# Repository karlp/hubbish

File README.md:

## Hubbish is not rubbish.

Hubbish is a USB 2.0 HS hub.  And?  It has per port power switching and overrcurrent shutoff.
And? It is designed for cascading, with 6 ports for user devices on the front, and ports
on each side for directly plugging together.  And? That's it.

## but why.gif?

Per port power switching was a goal.  Also, "this should be really simple!"
Also, to make the physical layout sensible for the desired use case.  Initially, this
project was conceived to be part of regression testing the USB stack for
[libopencm3](http://www.libopencm3.org).  The _minimal_ test setup there required 17
USB devices.  This is also why the ports are paired.  It's setup to have one port
for the DUT and one for the test driver.  They are otherwise completely independent.

That's all folks!

## Design goals
Cheap as shit, but fully functional. So, cheapest china compatible parts for everything,
but to avoid running into hub depth limits, and make config simpler, still using a
7 port hub, not attempting to cascade 4 port hubs.  Given that the original design goal requires
3 stacked hubs for 18 test ports, caascading hubs internally was not appealing.

Still, doing usb-hs on 2 layers requires fat traces and isolation to do properly, so this
setup is currently targetting jlcpcb's cheap as shit 4 layer 2313 stackup.

Oh, and design it to actually go in a case.

## Origins
This project was split out from the [libopencm3-tests](http://github.com/karlp/libopencm3-tests)
repository when it became apparent that it was it's own monster.

## Versions
### "r4" r2022-12
#### Status
Only on paper, mostly, uses a proper matched pair to "correctly" implement the auto vbus/5v switchiver. (I misunderstood the use of the matched pair, and just used two discrete transistors in overzealous BOM optimization.
TBD: fixes the pwoer good indicator on the main supply as well?
Still need to work on the "local power" portion a bit more fully? (or double check it?)

### "r3" r2022-10
#### Improvements
After a long hiatus, I decided to get back to it, and not even bother assembling the r2 boards I had gotten back.  I had already found some errors, which I can't remember entirely right now, so we just moved forward to r3:
This has a very overhauled BOM, to match JLC's assembly service, rather than just something to assemble myself by hand.
Some footprints change to suit this as well.

#### Status
This was built and assembled by JLC.  It works ok. It doesn't switch between bus powered and self powered very well, iirc.  The hub's "local power" flag isn't handled properly, and that's just my error.  The board still uses optional A-male or B-micro for the upstream USB connection, and "obviously" that should all be PD and type-C these days :)  maybe one day...
Finally, the dual colour leds chosen aren't really very good at showing two colours for low speed / full speed / high speed, particular the difference between FS and HS, which is the more interesting one.  Should revisit that, but I had enough on with this revision to not do more. The "Power Good" LED for the onboard DCDC supply doesn't work properly either, again, my error,  but not really critical.  Finally, the polarity protection FET is only rated to Vgs of 30V.  It's suggested (rightly) that this is really pushing it for a 24V design, and I should look for a better option there.

But, the 40W supply works! This is the biggest DCDC supply I'd ever made myself. (FIXME - add the picture of all the usb load testers plugged in) And not just works, it works and keeps cool, and you can deliver all that power to all 7 downstream ports, up to the limit of each of the load switches.

This design also just decided that programming the EEPROM was the _right_ thing to do, as it also lets you arrange the LEDs nicely to match the ports, and provide proper serial numbers, which are also an important part of a big cascaded port power switching design. [generatei2c.py] is a python script that generates commands for use with i2cutils to program the eeprom via the header.  I used the [i2c_tools example](https://github.com/espressif/esp-idf/tree/master/examples/peripherals/i2c/i2c_tools) on an ESP32 devboard to do this.  It's... very simplistic, but it's enough.

* 
* [Schematic-r3](r2022-10/hubbish-rev3-2022-10.pdf)
* Load testing all ports at once.  (I have thermal images, but have lost them... will have to retest)

### "r2" r2021-03  (lol, finished and ordered 2022-06)
#### Improvements:
Adds a 30-40ish Watt power supply.  Inductor is rated to 9A, regulator to 12A. Per port power switches are
still 1A nominal, so nominally 7x5x1 = 35W for the ports plus around .5x3.3 for the hub itself, or an extra say 2W.

Resizes to 100x80mm so cheaper manufacturing again.  We're no longer trying to find an off the shelf case.
Places like 3d craft cloud have gotten so cheap I'm going to just make a custom case and have it printed on demand.

What's it look like?

* [Schematic-r2](r2021-02/hubbish-rev2.pdf)

#### Bugs
This doesn't have ground connected for two caps on the 3v3 rail, and would have needed some bodge wires, but I seem to recall there being something else, to the point that I decided to not even bother assembling it, and just move on to a rev3, designed for JLC assembly.

### r2020-03
What's it look like?

* [Schematic-r1](r2020-03/usb-test-harness.pdf)

#### Bugs

1. Missing a serial resistor for the crystal.  Doesn't enumerate the hub without it.
1. Needs a jumper wire if yout want to actually run it as a bus powered hub for testing.
1. Port numbers are super wonky.
1. .... doesn't actually work?  I suspect I just have assembly issues, but...
1. Bigger than 100x100, which fits the Bud case nicely, and didn't matter when 4L was always just size based
   but now that jlc is doing 4L super cheap for under 100x100, this can be considered a bug
1. vertical (z axis) positioning of the usptream usb-a-male and downstream usb-a-female for chaining doesn't
   align properly.

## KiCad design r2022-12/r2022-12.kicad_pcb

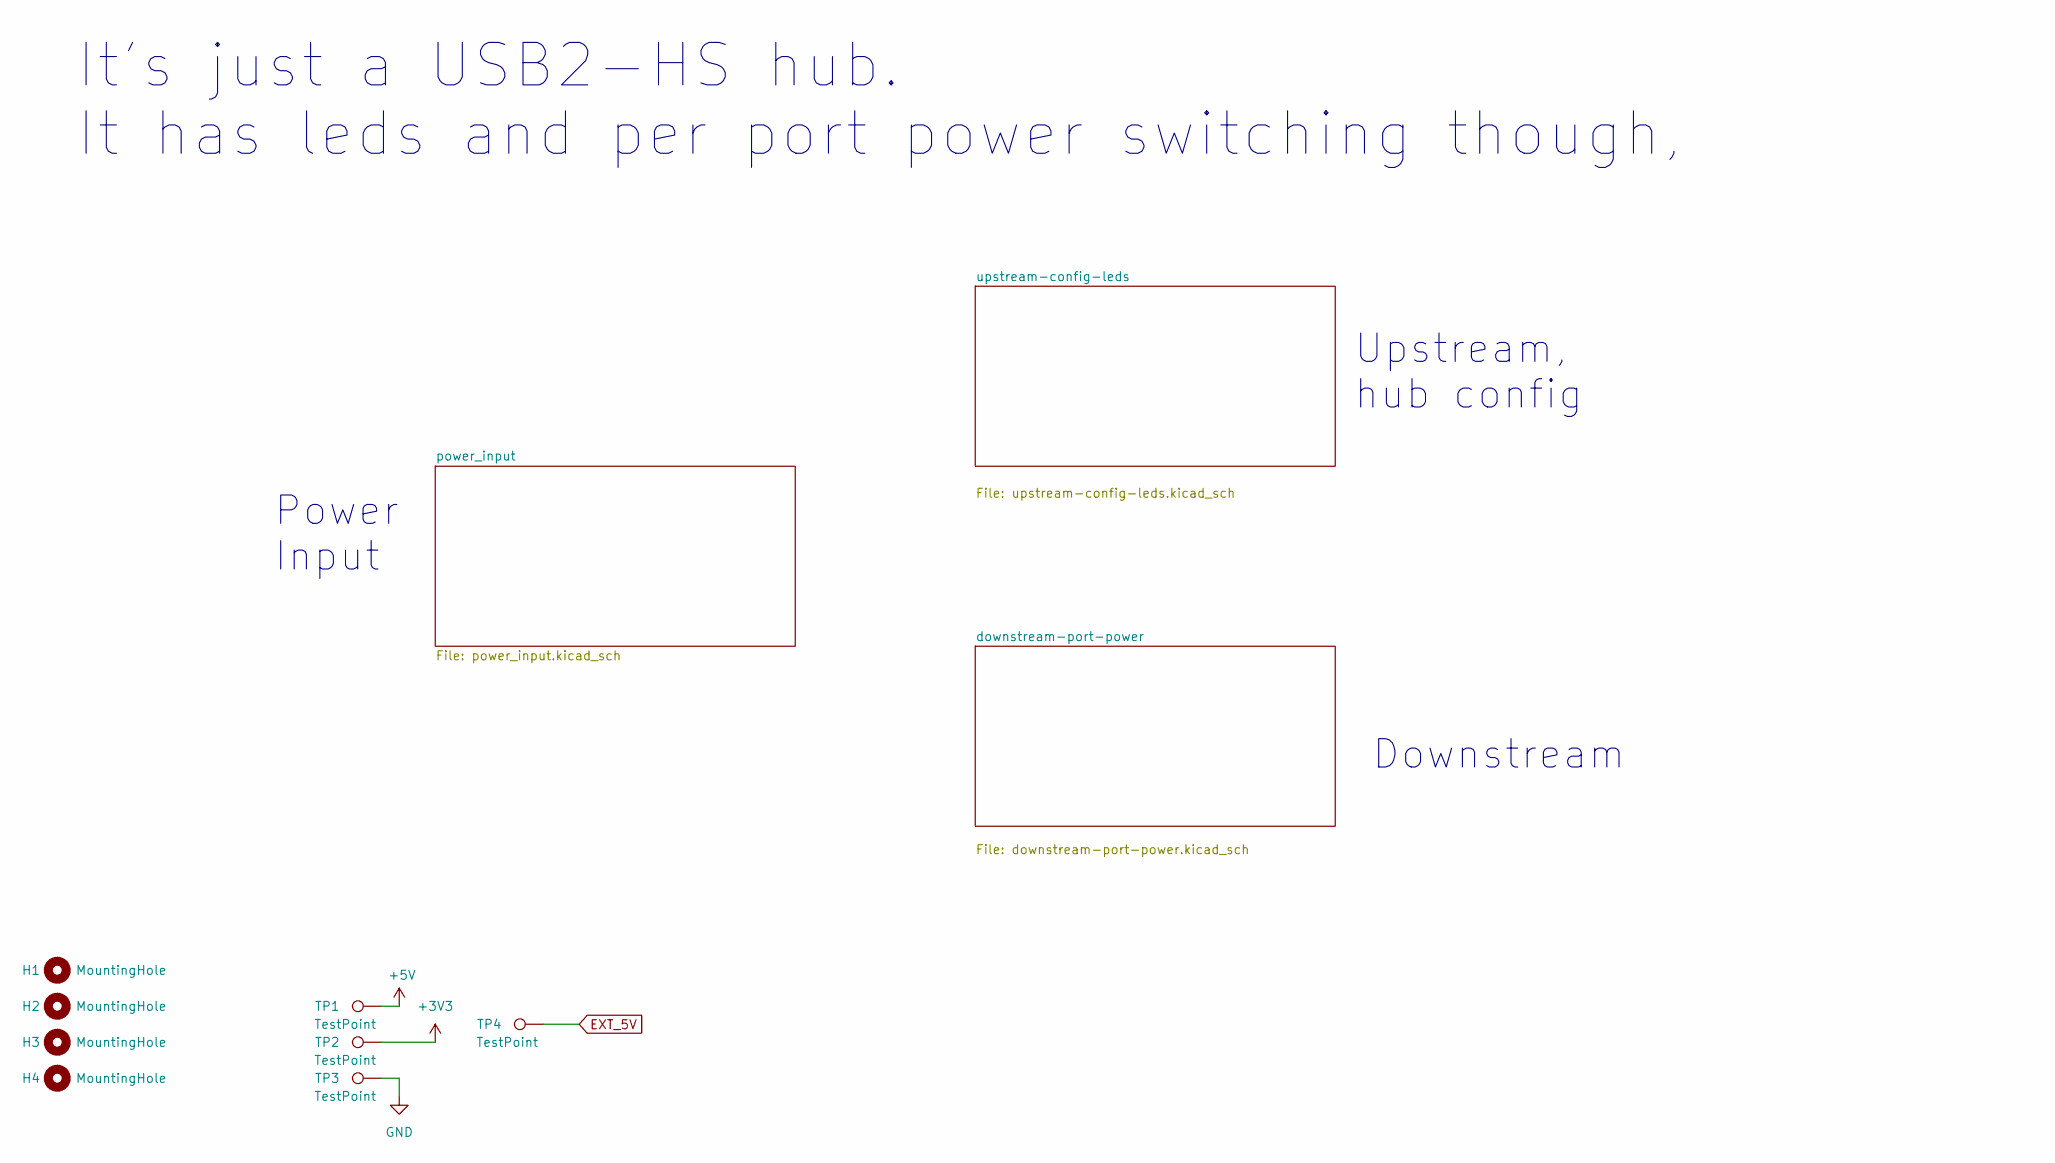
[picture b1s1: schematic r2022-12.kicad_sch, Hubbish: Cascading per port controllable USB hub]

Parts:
H1, H2, H3, H4: MountingHole; MountingHole_3.2mm_M3
TP1, TP2, TP3, TP4: TestPoint; TestPoint_Plated_Hole_0.6_D0.8mm

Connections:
+3V3: TP2.1; also elsewhere on the board
+5V: TP1.1; also elsewhere on the board
EXT_5V: TP4.1; also elsewhere on the board
GND: TP3.1; also elsewhere on the board

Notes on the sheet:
Upstream, hub config
Downstream
Power Input
It's just a USB2-HS hub. It has leds and per port power switching though,

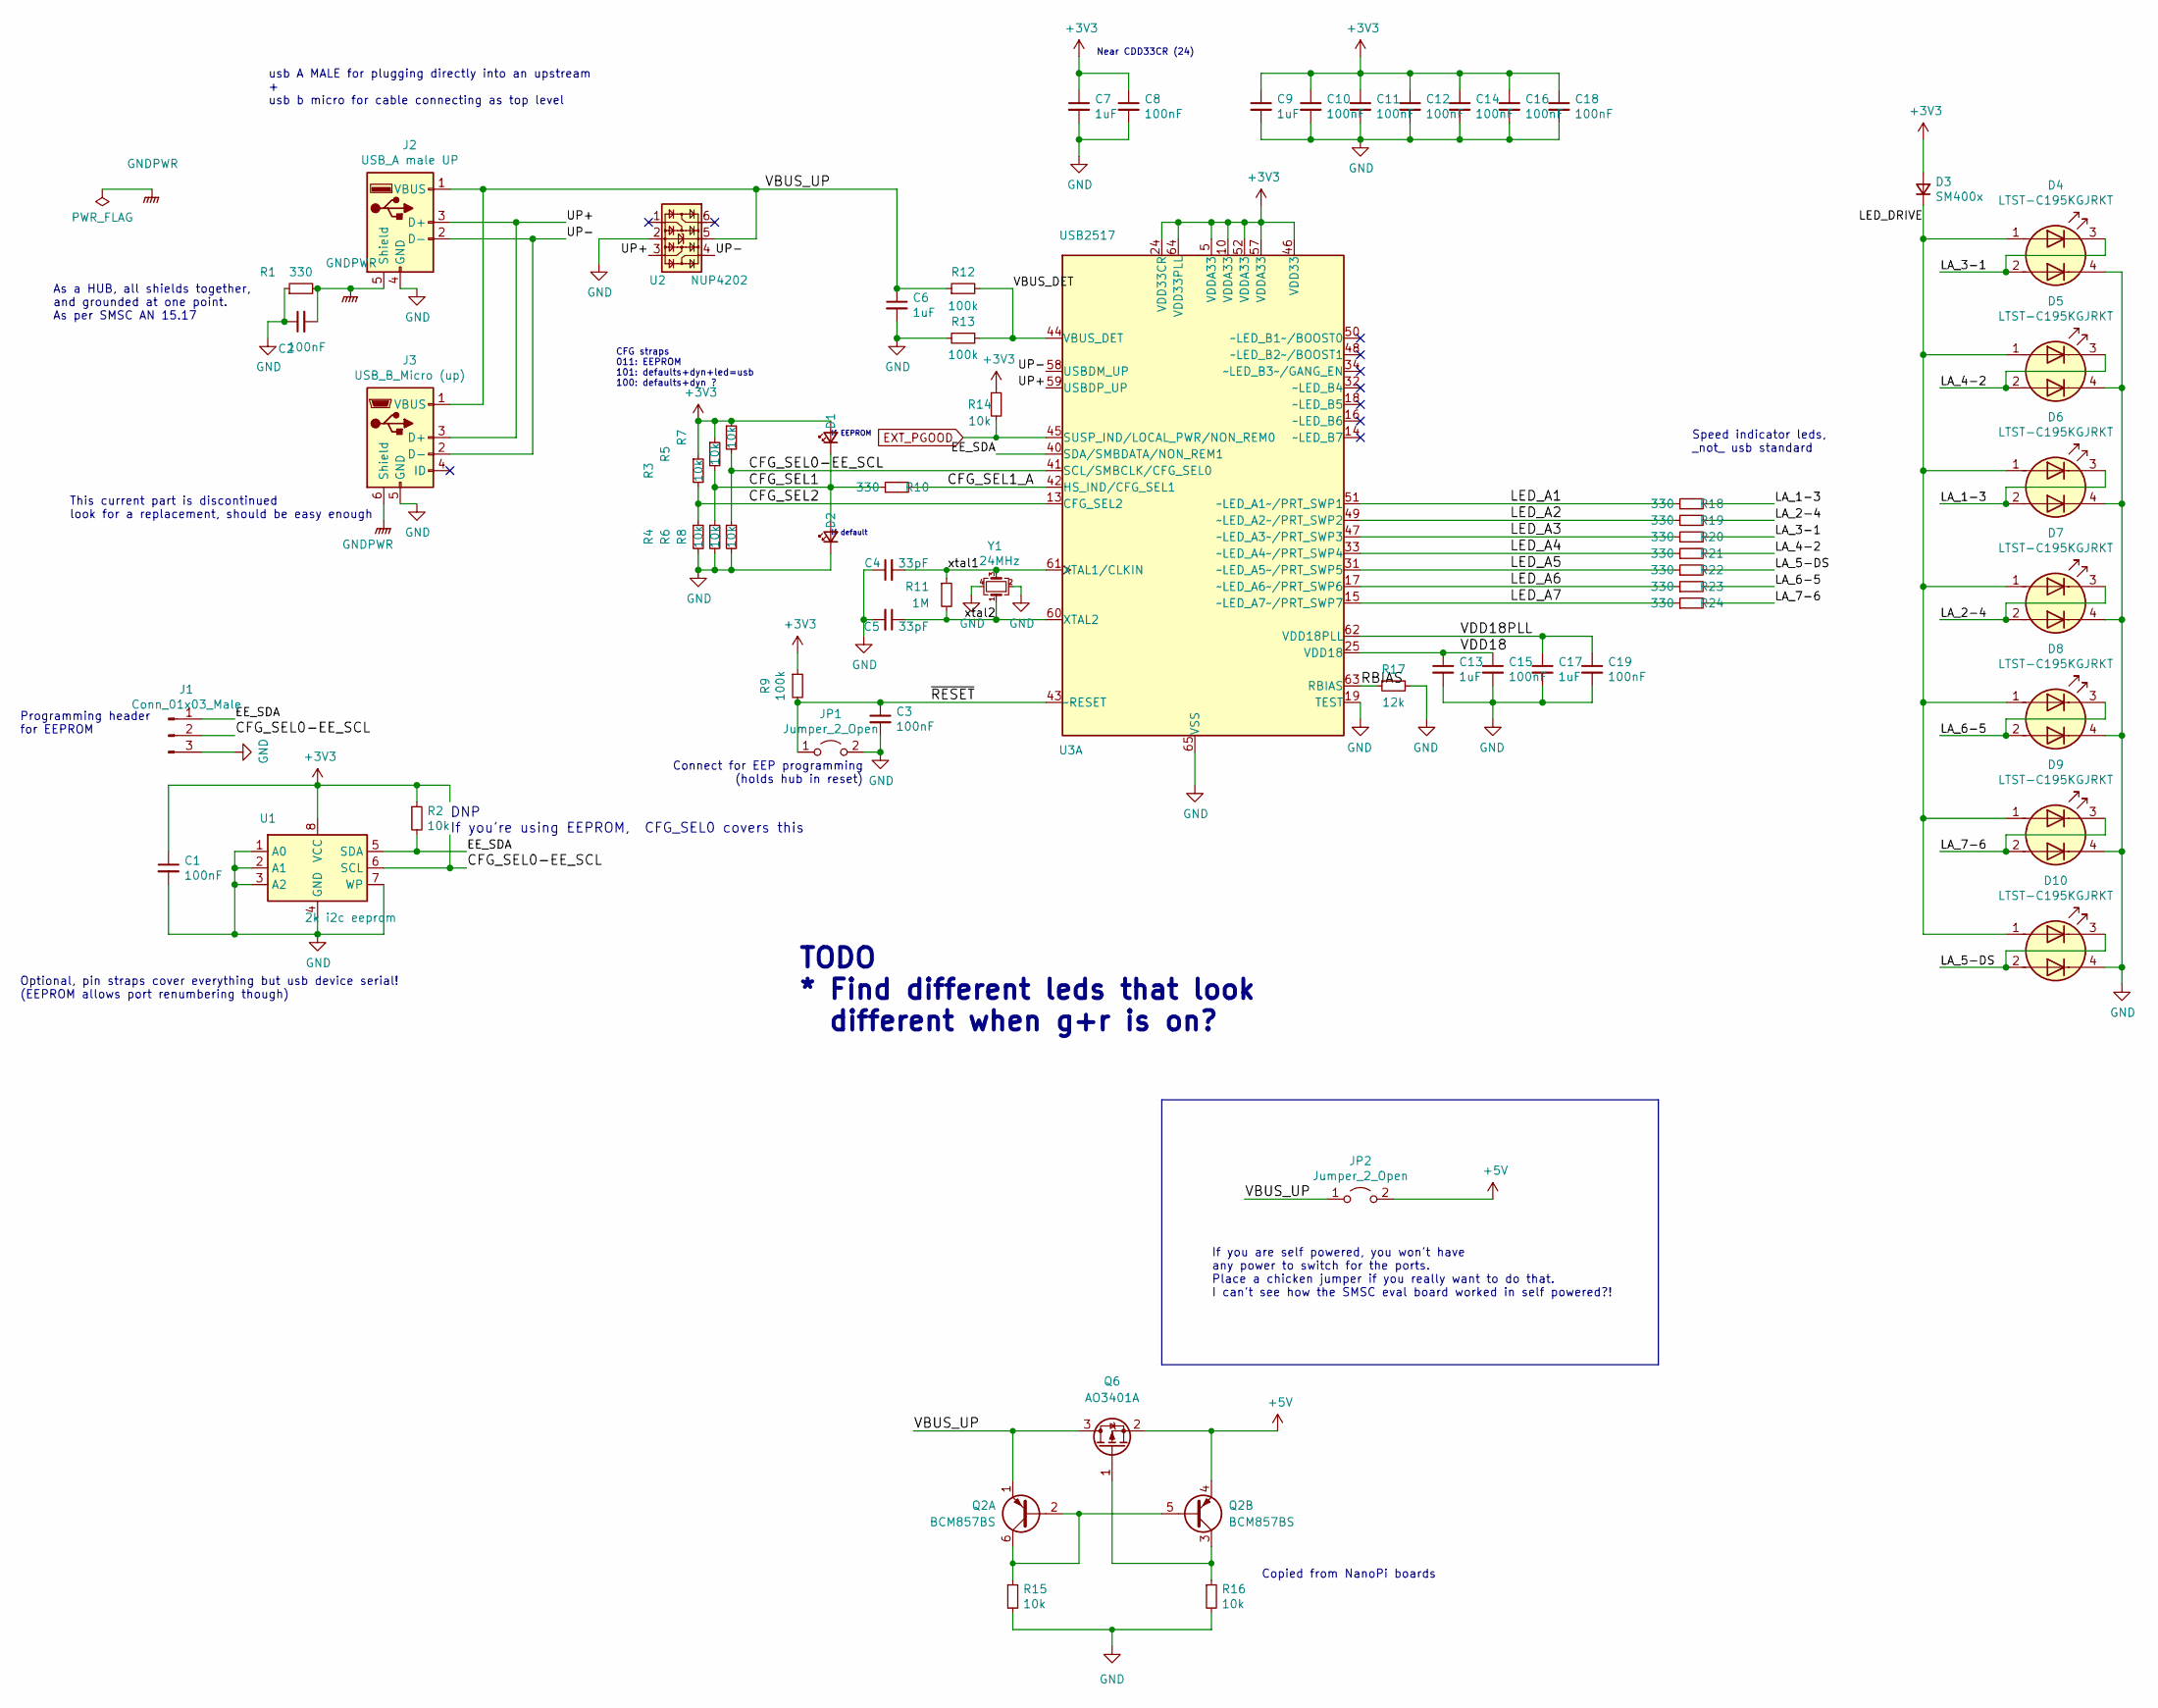
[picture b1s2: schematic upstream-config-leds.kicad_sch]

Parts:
C1, C2, C3, C8, C10, C11, C12, C14, C15, C16, C18, C19: 100nF; C_0603_1608Metric; MPN CC0603KRX7R9BB104; lcsc# C14663
C4, C5: 33pF; C_0603_1608Metric; MPN CL10C330JB8NNNC; jlc-basic 1
C6, C7, C9, C13, C17: 1uF; C_0603_1608Metric; MPN CL10A105KB8NNNC; jlc-basic 1
D1: HS1B; LED_0805_2012Metric; MPN NCD0805R1; jlc-basic 1
D2: HS1A; LED_0805_2012Metric; MPN NCD0805R1; jlc-basic 1
D3: SM400x; D_SOD-123F; MPN SM4007PL; jlc-basic 1
D4, D5, D6, D7, D8, D9, D10: LTST-C195KGJRKT; T1615_LiteOn_LTST_C195x; MPN LTST-C195KGJRKT; jlc-basic 0
J1: Conn_01x03_Male; PinHeader_1x03_P2.54mm_Vertical
J2: USB_A male UP; USB_A_Plug_SOFNG_USB-05; MPN SOFNG USB-05
J3: USB_B_Micro (up); USB_Micro-B_Amphenol_10118194-0001LF_Horizontal; MPN U254-051T-4BH23-S2B; jlc-basic 0
JP1, JP2: Jumper_2_Open; TestPoint_2Pads_Pitch2.54mm_Drill0.8mm
Q2: BCM857BS; SOT-363_SC-70-6; MPN BCM857BS-7-F; jlc-basic 0
Q6: AO3401A; SOT-23; MPN AO3401A; jlc-basic 1
R1, R10, R18, R19, R20, R21, R22, R23, R24: 330; R_0603_1608Metric; MPN 0603WAF3300T5E; jlc-basic 1
R2, R3, R4, R5, R6, R7, R8, R14, R15, R16: 10k; R_0603_1608Metric; MPN 0603WAF1002T5E; jlc-basic 1
R9, R12, R13: 100k; R_0603_1608Metric; MPN 0603WAF1003T5E; jlc-basic 1
R11: 1M; R_0603_1608Metric; MPN 0603WAF1004T5E; lcsc# C22935
R17: 12k; R_0603_1608Metric; MPN 0603WAF1202T5E; jlc-basic 1
U1: 2k i2c eeprom; SOIC-8_3.9x4.9mm_P1.27mm; MPN M24C02-WMN6TP; jlc-basic 1
U2: NUP4202; SOT-23-6; MPN SRV05-4-P-T7; jlc-basic 1
U3: USB2517; QFN-64-1EP_9x9mm_P0.5mm_EP4.7x4.7mm_ThermalVias; MPN USB2517I-JZX-TR; jlc-basic 0
Y1: 24MHz; Crystal_SMD_3225-4Pin_3.2x2.5mm; MPN X322524MOB4SI; jlc-basic 0

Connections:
+3V3: C1.1, C7.1, C8.1, C9.1, C10.1, C11.1, C12.1, C14.1, C16.1, C18.1, D1.2 (A), D3.2 (A), R2.1, R3.1, R5.1, R7.1, R9.1, R14.1, U1.8 (VCC), U3.5 (VDDA33), U3.10 (VDDA33), U3.24 (VDD33CR), U3.46 (VDD33), U3.52 (VDDA33), U3.57 (VDDA33), U3.64 (VDD33PLL); also elsewhere on the board
+5V: JP2.2 (B), Q2.4 (E2), Q6.2 (S); also elsewhere on the board
/upstream-config-leds/CFG_SEL0-EE_SCL: J1.2, R7.2, R8.1, U1.6 (SCL), U3.41 (SCL/SMBCLK/CFG_SEL0)
/upstream-config-leds/CFG_SEL1: D1.1 (K), D2.2 (A), R5.2, R6.1, R10.1
/upstream-config-leds/CFG_SEL1_A: R10.2, U3.42 (HS_IND/CFG_SEL1)
/upstream-config-leds/CFG_SEL2: R3.2, R4.1, U3.13 (CFG_SEL2)
/upstream-config-leds/EE_SDA: J1.1, R2.2, U1.5 (SDA), U3.40 (SDA/SMBDATA/NON_REM1)
/upstream-config-leds/LA_1-3: D6.2 (A2), D6.3 (K1), R18.2
/upstream-config-leds/LA_2-4: D7.2 (A2), D7.3 (K1), R19.2
/upstream-config-leds/LA_3-1: D4.2 (A2), D4.3 (K1), R20.2
/upstream-config-leds/LA_4-2: D5.2 (A2), D5.3 (K1), R21.2
/upstream-config-leds/LA_5-DS: D10.2 (A2), D10.3 (K1), R22.2
/upstream-config-leds/LA_6-5: D8.2 (A2), D8.3 (K1), R23.2
/upstream-config-leds/LA_7-6: D9.2 (A2), D9.3 (K1), R24.2
/upstream-config-leds/LED_A1: R18.1, U3.51 (~LED_A1~/PRT_SWP1)
/upstream-config-leds/LED_A2: R19.1, U3.49 (~LED_A2~/PRT_SWP2)
/upstream-config-leds/LED_A3: R20.1, U3.47 (~LED_A3~/PRT_SWP3)
/upstream-config-leds/LED_A4: R21.1, U3.33 (~LED_A4~/PRT_SWP4)
/upstream-config-leds/LED_A5: R22.1, U3.31 (~LED_A5~/PRT_SWP5)
/upstream-config-leds/LED_A6: R23.1, U3.17 (~LED_A6~/PRT_SWP6)
/upstream-config-leds/LED_A7: R24.1, U3.15 (~LED_A7~/PRT_SWP7)
/upstream-config-leds/LED_DRIVE: D3.1 (K), D4.1 (A1), D5.1 (A1), D6.1 (A1), D7.1 (A1), D8.1 (A1), D9.1 (A1), D10.1 (A1)
/upstream-config-leds/RBIAS: R17.1, U3.63 (RBIAS)
/upstream-config-leds/UP+: J2.3 (D+), J3.3 (D+), U2.3, U3.59 (USBDP_UP)
/upstream-config-leds/UP-: J2.2 (D-), J3.2 (D-), U2.4, U3.58 (USBDM_UP)
/upstream-config-leds/VBUS_DET: R12.2, R13.1, U3.44 (VBUS_DET)
/upstream-config-leds/VBUS_UP: C6.1, J2.1 (VBUS), J3.1 (VBUS), JP2.1 (A), Q2.1 (E1), Q6.3 (D), R12.1, U2.5
/upstream-config-leds/VDD18: C13.1, C15.1, U3.25 (VDD18)
/upstream-config-leds/VDD18PLL: C17.1, C19.1, U3.62 (VDD18PLL)
/upstream-config-leds/xtal1: C4.2, R11.1, U3.61 (XTAL1/CLKIN), Y1.3
/upstream-config-leds/xtal2: C5.1, R11.2, U3.60 (XTAL2), Y1.1
/upstream-config-leds/~RESET: C3.1, JP1.1 (A), R9.2, U3.43 (~RESET)
EXT_PGOOD: R14.2, U3.45 (SUSP_IND/LOCAL_PWR/NON_REM0); also elsewhere on the board
GND: C1.2, C2.1, C3.2, C4.1, C5.2, C6.2, C7.2, C8.2, C9.2, C10.2, C11.2, C12.2, C13.2, C14.2, C15.2, C16.2, C17.2, C18.2, C19.2, D2.1 (K), D4.4 (K2), D5.4 (K2), D6.4 (K2), D7.4 (K2), D8.4 (K2), D9.4 (K2), D10.4 (K2), J1.3, J2.4 (GND), J3.5 (GND), JP1.2 (B), R1.1, R4.2, R6.2, R8.2, R13.2, R15.2, R16.2, R17.2, U1.1 (A0), U1.2 (A1), U1.3 (A2), U1.4 (GND), U1.7 (WP), U2.2, U3.19 (TEST), U3.65 (VSS), Y1.2, Y1.4; also elsewhere on the board
GNDPWR: C2.2, J2.5 (Shield), J3.6 (Shield), R1.2; also elsewhere on the board
unnamed: Q2.3 (C2), Q6.1 (G), R16.1
unnamed: Q2.2 (B1), Q2.5 (B2), Q2.6 (C1), R15.1

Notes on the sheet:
If default
If EEPROM
usb A MALE for plugging directly into an upstream + usb b micro for cable connecting as top level
DNP If you're using EEPROM, CFG_SEL0 covers this
CFG straps 011: EEPROM 101: defaults+dyn+led=usb 100: defaults+dyn ?
Copied from NanoPi boards
TODO * Find different leds that look different when g+r is on?
Speed indicator leds, _not_ usb standard
If you are self powered, you won't have any power to switch for the ports. Place a chicken jumper if you really want to do that. I can't see how the SMSC eval board worked in self powered?!
Near CDD33CR (24)
As a HUB, all shields together, and grounded at one point. As per SMSC AN 15.17
Optional, pin straps cover everything but usb device serial! (EEPROM allows port renumbering though)
Programming header for EEPROM
Connect for EEP programming (holds hub in reset)
This current part is discontinued look for a replacement, should be easy enough

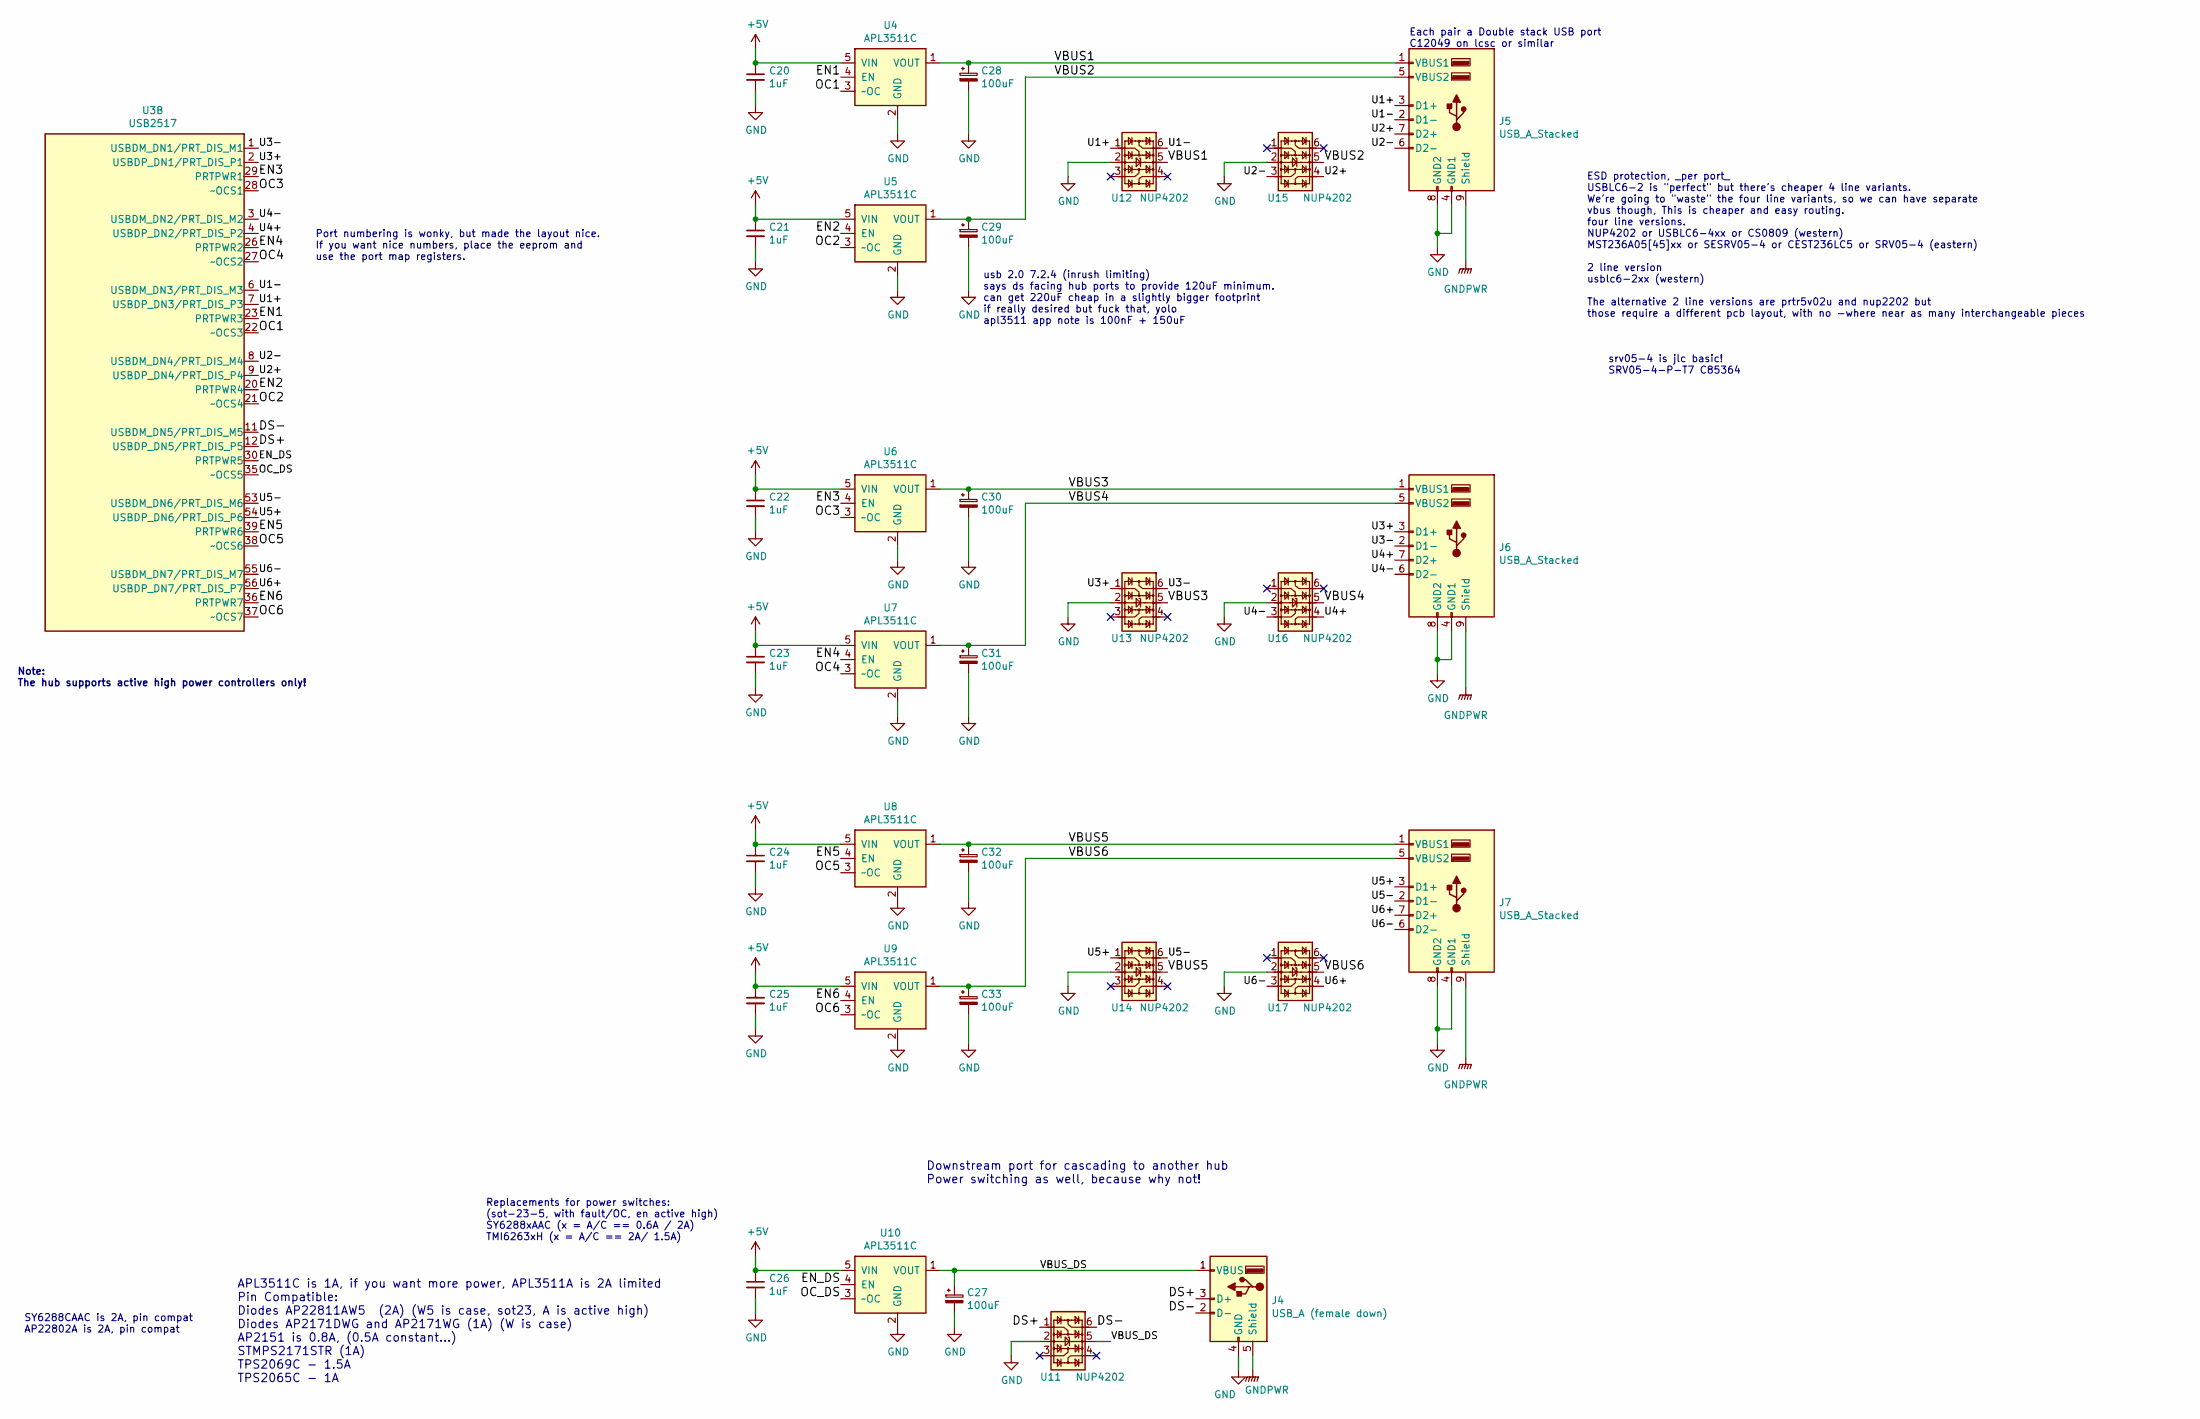
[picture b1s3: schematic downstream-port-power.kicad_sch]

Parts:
C20, C21, C22, C23, C24, C25, C26: 1uF; C_0603_1608Metric; MPN CL10A105KB8NNNC; jlc-basic 1
C27, C28, C29, C30, C31, C32, C33: 100uF; C_1206_3216Metric; MPN CL31A107MQHNNNE; jlc-basic 1
J4: USB_A (female down); USB_A_Stewart_SS-52100-001_Horizontal; MPN 902-141A1011D10100; jlc-basic 0
J5, J6, J7: USB_A_Stacked; USB_A_Wuerth_61400826021_Horizontal_Stacked; MPN 907-111A1012D10200; jlc-basic 0
U3: USB2517; QFN-64-1EP_9x9mm_P0.5mm_EP4.7x4.7mm_ThermalVias; MPN USB2517I-JZX-TR; jlc-basic 0
U4, U5, U6, U7, U8, U9, U10: APL3511C; SOT-23-5; MPN AP22802AW5-7; jlc-basic 0
U11, U12, U13, U14, U15, U16, U17: NUP4202; SOT-23-6; MPN SRV05-4-P-T7; jlc-basic 1

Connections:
+5V: C20.1, C21.1, C22.1, C23.1, C24.1, C25.1, C26.1, U4.5 (VIN), U5.5 (VIN), U6.5 (VIN), U7.5 (VIN), U8.5 (VIN), U9.5 (VIN), U10.5 (VIN); also elsewhere on the board
/downstream-port-power/DS+: J4.3 (D+), U3.12 (USBDP_DN5/PRT_DIS_P5), U11.1
/downstream-port-power/DS-: J4.2 (D-), U3.11 (USBDM_DN5/PRT_DIS_M5), U11.6
/downstream-port-power/EN1: U3.23 (PRTPWR3), U4.4 (EN)
/downstream-port-power/EN2: U3.20 (PRTPWR4), U5.4 (EN)
/downstream-port-power/EN3: U3.29 (PRTPWR1), U6.4 (EN)
/downstream-port-power/EN4: U3.26 (PRTPWR2), U7.4 (EN)
/downstream-port-power/EN5: U3.39 (PRTPWR6), U8.4 (EN)
/downstream-port-power/EN6: U3.36 (PRTPWR7), U9.4 (EN)
/downstream-port-power/EN_DS: U3.30 (PRTPWR5), U10.4 (EN)
/downstream-port-power/OC1: U3.22 (~OCS3), U4.3 (~OC)
/downstream-port-power/OC2: U3.21 (~OCS4), U5.3 (~OC)
/downstream-port-power/OC3: U3.28 (~OCS1), U6.3 (~OC)
/downstream-port-power/OC4: U3.27 (~OCS2), U7.3 (~OC)
/downstream-port-power/OC5: U3.38 (~OCS6), U8.3 (~OC)
/downstream-port-power/OC6: U3.37 (~OCS7), U9.3 (~OC)
/downstream-port-power/OC_DS: U3.35 (~OCS5), U10.3 (~OC)
/downstream-port-power/U1+: J5.3 (D1+), U3.7 (USBDP_DN3/PRT_DIS_P3), U12.1
/downstream-port-power/U1-: J5.2 (D1-), U3.6 (USBDM_DN3/PRT_DIS_M3), U12.6
/downstream-port-power/U2+: J5.7 (D2+), U3.9 (USBDP_DN4/PRT_DIS_P4), U15.4
/downstream-port-power/U2-: J5.6 (D2-), U3.8 (USBDM_DN4/PRT_DIS_M4), U15.3
/downstream-port-power/U3+: J6.3 (D1+), U3.2 (USBDP_DN1/PRT_DIS_P1), U13.1
/downstream-port-power/U3-: J6.2 (D1-), U3.1 (USBDM_DN1/PRT_DIS_M1), U13.6
/downstream-port-power/U4+: J6.7 (D2+), U3.4 (USBDP_DN2/PRT_DIS_P2), U16.4
/downstream-port-power/U4-: J6.6 (D2-), U3.3 (USBDM_DN2/PRT_DIS_M2), U16.3
/downstream-port-power/U5+: J7.3 (D1+), U3.54 (USBDP_DN6/PRT_DIS_P6), U14.1
/downstream-port-power/U5-: J7.2 (D1-), U3.53 (USBDM_DN6/PRT_DIS_M6), U14.6
/downstream-port-power/U6+: J7.7 (D2+), U3.56 (USBDP_DN7/PRT_DIS_P7), U17.4
/downstream-port-power/U6-: J7.6 (D2-), U3.55 (USBDM_DN7/PRT_DIS_M7), U17.3
/downstream-port-power/VBUS1: C28.1, J5.1 (VBUS1), U4.1 (VOUT), U12.5
/downstream-port-power/VBUS2: C29.1, J5.5 (VBUS2), U5.1 (VOUT), U15.5
/downstream-port-power/VBUS3: C30.1, J6.1 (VBUS1), U6.1 (VOUT), U13.5
/downstream-port-power/VBUS4: C31.1, J6.5 (VBUS2), U7.1 (VOUT), U16.5
/downstream-port-power/VBUS5: C32.1, J7.1 (VBUS1), U8.1 (VOUT), U14.5
/downstream-port-power/VBUS6: C33.1, J7.5 (VBUS2), U9.1 (VOUT), U17.5
/downstream-port-power/VBUS_DS: C27.1, J4.1 (VBUS), U10.1 (VOUT), U11.5
GND: C20.2, C21.2, C22.2, C23.2, C24.2, C25.2, C26.2, C27.2, C28.2, C29.2, C30.2, C31.2, C32.2, C33.2, J4.4 (GND), J5.4 (GND1), J5.8 (GND2), J6.4 (GND1), J6.8 (GND2), J7.4 (GND1), J7.8 (GND2), U4.2 (GND), U5.2 (GND), U6.2 (GND), U7.2 (GND), U8.2 (GND), U9.2 (GND), U10.2 (GND), U11.2, U12.2, U13.2, U14.2, U15.2, U16.2, U17.2; also elsewhere on the board
GNDPWR: J4.5 (Shield), J5.9 (Shield), J6.9 (Shield), J7.9 (Shield); also elsewhere on the board

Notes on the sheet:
Note: The hub supports active high power controllers only!
Downstream port for cascading to another hub Power switching as well, because why not!
srv05-4 is jlc basic! SRV05-4-P-T7 C85364
usb 2.0 7.2.4 (inrush limiting) says ds facing hub ports to provide 120uF minimum. can get 220uF cheap in a slightly bigger footprint if really desired but fuck that, yolo apl3511 app note is 100nF + 150uF
Each pair a Double stack USB port C12049 on lcsc or similar
Replacements for power switches: (sot-23-5, with fault/OC, en active high) SY6288xAAC (x = A/C == 0.6A / 2A) TMI6263xH (x = A/C == 2A/ 1.5A)
SY6288CAAC is 2A, pin compat AP22802A is 2A, pin compat
APL3511C is 1A, if you want more power, APL3511A is 2A limited Pin Compatible: Diodes AP22811AW5 (2A) (W5 is case, sot23, A is active high) Diodes AP2171DWG and AP2171WG (1A) (W is case) AP2151 is 0.8A, (0.5A constant...) STMPS2171STR (1A) TPS2069C - 1.5A TPS2065C - 1A
ESD protection, _per port_ USBLC6-2 is "perfect" but there's cheaper 4 line variants. We're going to "waste" the four line variants, so we can have separate vbus though, This is cheaper and easy routing. four line versions. NUP4202 or USBLC6-4xx or CS0809 (western) MST236A05[45]xx or SESRV05-4 or C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
Port numbering is wonky, but made the layout nice. If you want nice numbers, place the eeprom and use the port map registers.

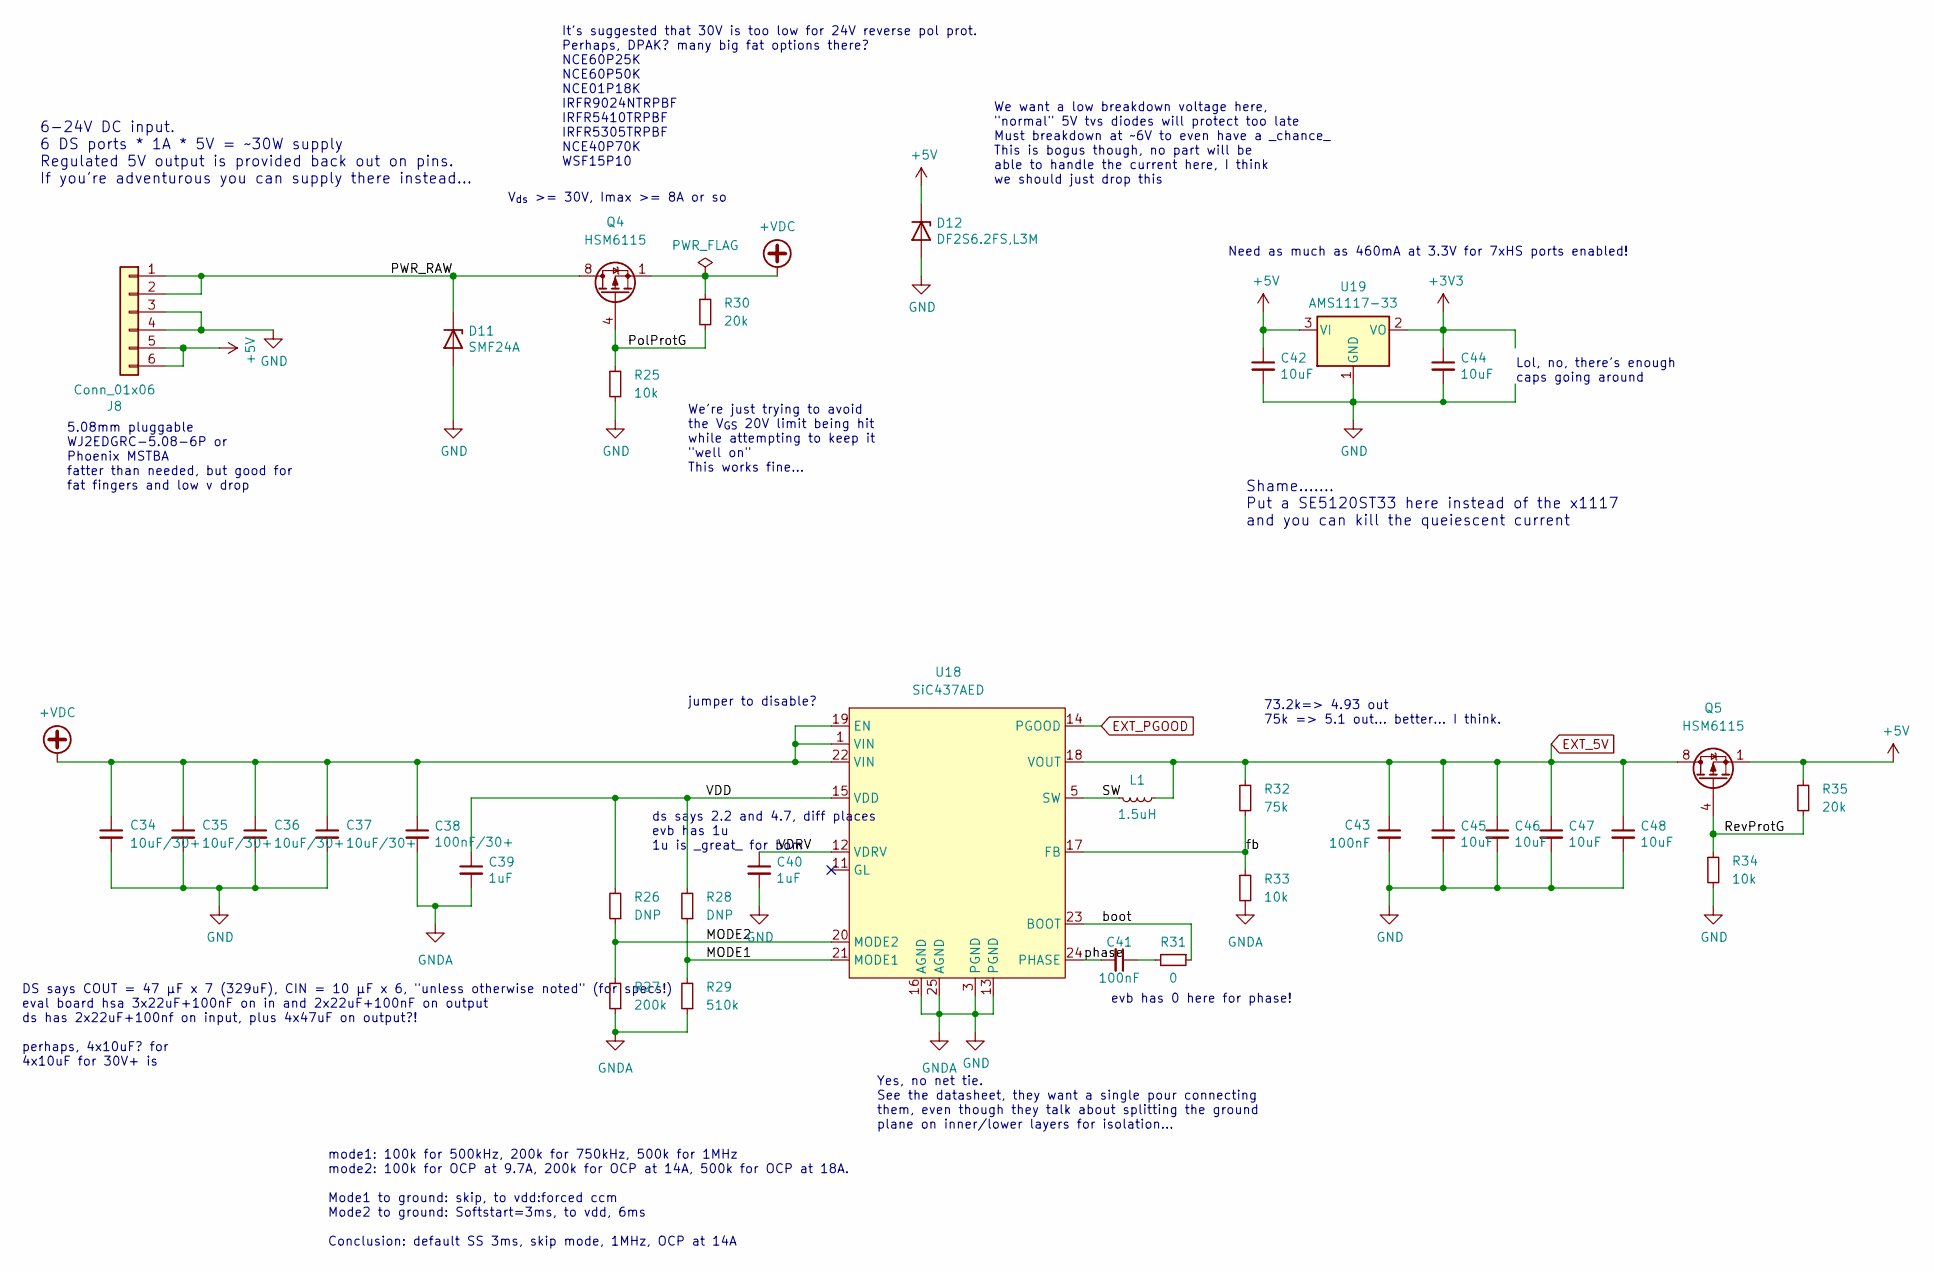
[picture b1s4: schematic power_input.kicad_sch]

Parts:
C34, C35, C36, C37: 10uF/30+; C_1206_3216Metric; MPN CL31A106KBHNNNE; lcsc# C13585
C38: 100nF/30+; C_0603_1608Metric; MPN CC0603KRX7R9BB104; lcsc# C14663
C39, C40: 1uF; C_0603_1608Metric; MPN CL10A105KB8NNNC; jlc-basic 1
C41, C43: 100nF; C_0603_1608Metric; MPN CC0603KRX7R9BB104; lcsc# C14663
C42, C44, C45, C46, C47, C48: 10uF; C_0805_2012Metric; MPN CL21A106KAYNNNE; lcsc# C15850
D11: SMF24A; D_SOD-123F; MPN SMF24A; jlc-basic 0
D12: DF2S6.2FS,L3M; D_SOD-923
J8: Conn_01x06; PhoenixContact_MSTBA_2,5_6-G-5,08_1x06_P5.08mm_Horizontal
L1: 1.5uH; L_Chilisin_BMRx00060630; MPN MHCI06030-1R5M-R8A; jlc-basic 0
Q4, Q5: HSM6115; SOIC-8_3.9x4.9mm_P1.27mm; MPN HSM6115; jlc-basic 0
R25, R33, R34: 10k; R_0603_1608Metric; MPN 0603WAF1002T5E; jlc-basic 1
R26, R28: DNP; R_0603_1608Metric
R27: 200k; R_0603_1608Metric; MPN 0603WAF2003T5E; jlc-basic 1
R29: 510k; R_0603_1608Metric; MPN 0603WAF5103T5E; lcsc# C23192
R30, R35: 20k; R_0603_1608Metric; MPN 0603WAF2002T5E; jlc-basic 1
R31: 0; R_0603_1608Metric; MPN 0603WAF0000T5E; jlc-basic 1
R32: 75k; R_0603_1608Metric; MPN 0603WAF7502T5E; jlc-basic 1
U18: SiC437AED; Vishay_MLP-44L_4x4; MPN SIC437AED-T1-GE3; jlc-basic 0
U19: AMS1117-33; SOT-223-3_TabPin2; MPN AMS1117-33; jlc-basic 1

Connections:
+3V3: C44.1, U19.2 (VO); also elsewhere on the board
+5V: C42.1, D12.1 (K), J8.5, J8.6, Q5.1 (S), Q5.2 (S), Q5.3 (S), R35.1, U19.3 (VI); also elsewhere on the board
+VDC: C34.1, C35.1, C36.1, C37.1, C38.1, Q4.1 (S), Q4.2 (S), Q4.3 (S), R30.1, U18.1 (VIN), U18.19 (EN), U18.22 (VIN)
/power_input/MODE1: R28.1, R29.2, U18.21 (MODE1)
/power_input/MODE2: R26.1, R27.2, U18.20 (MODE2)
/power_input/PWR_RAW: D11.1 (K), J8.1, J8.2, Q4.5 (D), Q4.6 (D), Q4.7 (D), Q4.8 (D)
/power_input/PolProtG: Q4.4 (G), R25.1, R30.2
/power_input/RevProtG: Q5.4 (G), R34.1, R35.2
/power_input/SW: L1.2, U18.5 (SW)
/power_input/VDD: C39.1, R26.2, R28.2, U18.15 (VDD)
/power_input/VDRV: C40.1, U18.12 (VDRV)
/power_input/boot: R31.1, U18.23 (BOOT)
/power_input/fb: R32.2, R33.1, U18.17 (FB)
/power_input/phase: C41.2, U18.24 (PHASE)
EXT_5V: C43.1, C45.1, C46.1, C47.1, C48.1, L1.1, Q5.5 (D), Q5.6 (D), Q5.7 (D), Q5.8 (D), R32.1, U18.18 (VOUT); also elsewhere on the board
EXT_PGOOD: U18.14 (PGOOD); also elsewhere on the board
GND: C34.2, C35.2, C36.2, C37.2, C38.2, C39.2, C40.2, C42.2, C43.2, C44.2, C45.2, C46.2, C47.2, C48.2, D11.2 (A), D12.2 (A), J8.3, J8.4, R25.2, R27.1, R29.1, R33.2, R34.2, U18.3 (PGND), U18.13 (PGND), U18.16 (AGND), U18.25 (AGND), U19.1 (GND); also elsewhere on the board
unnamed: C41.1, R31.2

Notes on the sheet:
We want a low breakdown voltage here, "normal" 5V tvs diodes will protect too late Must breakdown at ~6V to even have a _chance_ This is bogus though, no part will be able to handle the current here, I think we should just drop this
jumper to disable?
6-24V DC input. 6 DS ports * 1A * 5V = ~30W supply Regulated 5V output is provided back out on pins. If you're adventurous you can supply there instead...
Shame....... Put a SE5120ST33 here instead of the x1117 and you can kill the queiescent current
mode1: 100k for 500kHz, 200k for 750kHz, 500k for 1MHz mode2: 100k for OCP at 9.7A, 200k for OCP at 14A, 500k for OCP at 18A. Mode1 to ground: skip, to vdd:forced ccm Mode2 to ground: Softstart=3ms, to vdd, 6ms Conclusion: default SS 3ms, skip mode, 1MHz, OCP at 14A
73.2k=> 4.93 out 75k => 5.1 out... better... I think.
Need as much as 460mA at 3.3V for 7xHS ports enabled!
DS says COUT = 47 μF x 7 (329uF), CIN = 10 μF x 6, "unless otherwise noted" (for specs!) eval board hsa 3x22uF+100nF on in and 2x22uF+100nF on output ds has 2x22uF+100nf on input, plus 4x47uF on output?! perhaps, 4x10uF? for 4x10uF for 30V+ is
V_{ds} >= 30V, Imax >= 8A or so
Lol, no, there's enough caps going around
evb has 0 here for phase!
We're just trying to avoid the V_{GS} 20V limit being hit while attempting to keep it "well on" This works fine...
ds says 2.2 and 4.7, diff places evb has 1u 1u is _great_ for bom
It's suggested that 30V is too low for 24V reverse pol prot. Perhaps, DPAK? many big fat options there? NCE60P25K NCE60P50K NCE01P18K IRFR9024NTRPBF IRFR5410TRPBF IRFR5305TRPBF NCE40P70K WSF15P10
Yes, no net tie. See the datasheet, they want a single pour connecting them, even though they talk about splitting the ground plane on inner/lower layers for isolation...
5.08mm pluggable WJ2EDGRC-5.08-6P or Phoenix MSTBA fatter than needed, but good for fat fingers and low v drop
